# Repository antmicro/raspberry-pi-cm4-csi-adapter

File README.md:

# Antmicro's Raspberry Pi CM4 CSI adapter

Copyright (c) 2022 [Antmicro](https://www.antmicro.com)

## Overview

This repository contains open hardware design files for an adapter board allowing to connect video accessories developed by Antmicro to a Raspberry Pi CM4 IO Board over a 22-pin FFC connector.
The adapter allows to connect a 4-lane MIPI CSI-2 video interface along with power supply rail and I2C bus.  
The design files were prepared in KiCad.

## Repository structure

The main repository directory contains KiCad PCB project files, a LICENSE and README.
The remaining files are stored in the following directories:

* `lib` - contains the component libraries
* `img` - contains graphics for this README

## Key Features

* 50-pin FFC connector compatible with video accessories developed by Antmicro
* 22-pin FFC connector compatible with CSI video interface exposed on Raspberry Pi CM4 IO board
* Testpoints and jumper resistors for debugging the I2C communication

This adapter is electrically compatible with several video accessories created by Antmicro such as:
 
* [OV9281 Dual Camera Board](https://github.com/antmicro/ov9281-camera-board)
* [SDI-MIPI bridge](https://github.com/antmicro/sdi-mipi-bridge)
* [HDMI-MIPI bridge](https://github.com/antmicro/hdmi-mipi-bridge)

## License

[Apache-2.0](LICENSE)

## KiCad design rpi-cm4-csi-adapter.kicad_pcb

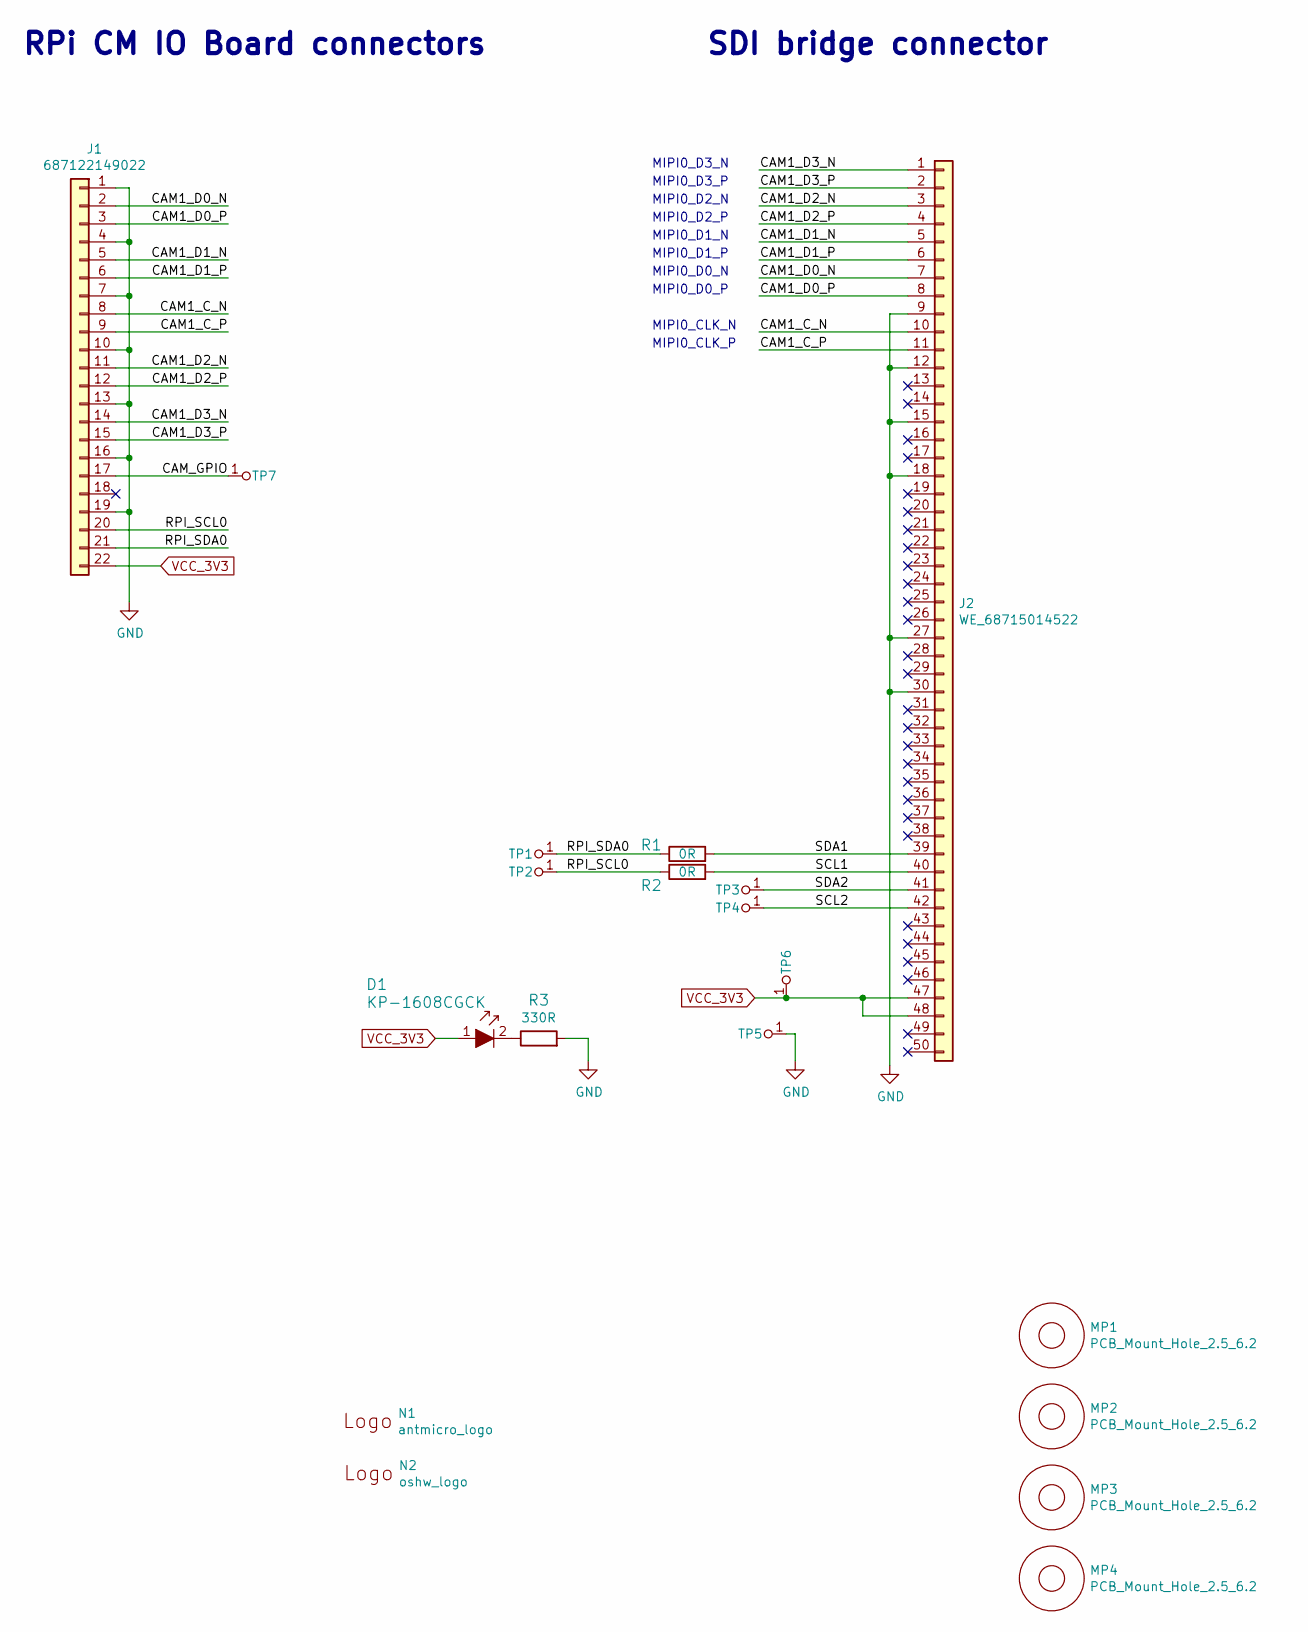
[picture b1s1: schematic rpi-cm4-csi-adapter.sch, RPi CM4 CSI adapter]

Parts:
D1: KP-1608CGCK; LED_0603; MPN KP-1608CGCK
J1: 687122149022; MPN 687122149022
J2: WE_68715014522; MPN 68715014522
MP1, MP2, MP3, MP4: PCB_Mount_Hole_2.5_6.2; Mount-hole-M2.5
N1: antmicro_logo; antmicro-logo_scaled_12mm
N2: oshw_logo; oshw-logo
R1, R2: R_0R_0402; 0402-res; MPN ERJ2GE0R00X
R3: R_330R_0402; 0402-res; MPN MCMR04X3300FTL
TP1, TP2, TP3, TP4, TP5, TP6, TP7: TP; TP-R-1.5

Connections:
/CAM1_C_N: J1.8, J2.10
/CAM1_C_P: J1.9, J2.11
/CAM1_D0_N: J1.2, J2.7
/CAM1_D0_P: J1.3, J2.8
/CAM1_D1_N: J1.5, J2.5
/CAM1_D1_P: J1.6, J2.6
/CAM1_D2_N: J1.11, J2.3
/CAM1_D2_P: J1.12, J2.4
/CAM1_D3_N: J1.14, J2.1
/CAM1_D3_P: J1.15, J2.2
/CAM_GPIO: J1.17, TP7.1
/RPI_SCL0: J1.20, R2.1, TP2.1
/RPI_SDA0: J1.21, R1.1, TP1.1
/SCL1: J2.40, R2.2
/SCL2: J2.42, TP4.1
/SDA1: J2.39, R1.2
/SDA2: J2.41, TP3.1
GND: J1.1, J1.4, J1.7, J1.10, J1.13, J1.16, J1.19, J2.9, J2.12, J2.15, J2.18, J2.27, J2.30, R3.2, TP5.1
unnamed: D1.2, R3.1
VCC_3V3: D1.1, J1.22, J2.47, J2.48, TP6.1

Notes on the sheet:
SDI bridge connector
RPi CM IO Board connectors
MIPI0_D1_N
MIPI0_D1_P
MIPI0_D0_N
MIPI0_D0_P
MIPI0_CLK_N
MIPI0_CLK_P
MIPI0_D2_P
MIPI0_D2_N
MIPI0_D3_P
MIPI0_D3_N

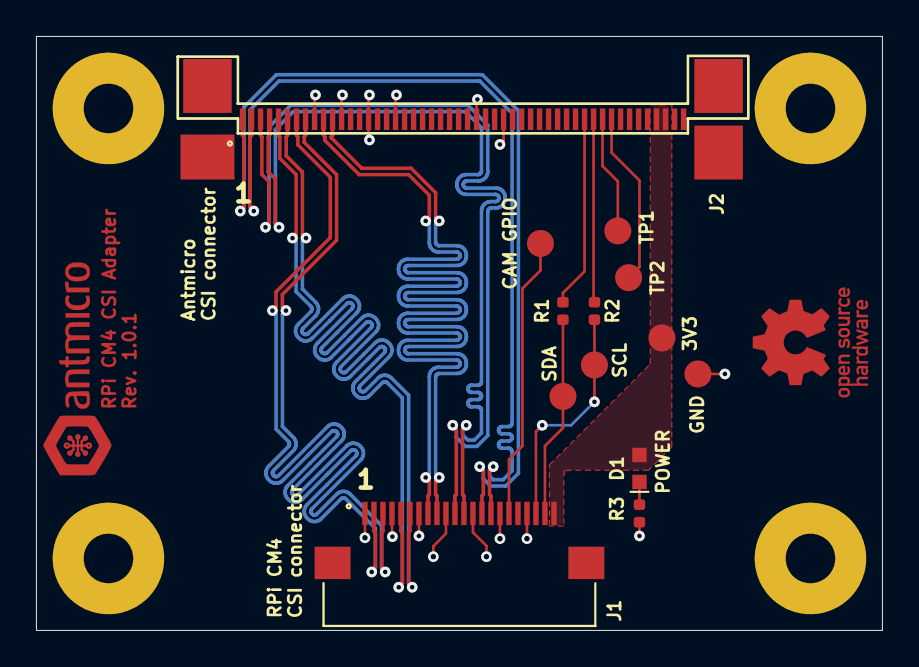
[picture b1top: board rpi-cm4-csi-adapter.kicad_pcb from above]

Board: 4 copper layers, 47.0 x 33.0 mm, 19 parts (0 on the bottom side), 20 nets.

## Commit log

2022-08-09 Initial commit.
2022-08-09 Make 687122149022 a SMT component
2022-08-09 Generate local libraries
2022-08-09 Swap I2C lines - bump revision to 1.0.1
2022-08-09 Add KiCad 6.0 project
2022-08-09 Add LICENSE
2022-08-09 Add README
2022-08-09 Add a photo with black background
2022-09-22 Notes added by 'git notes add'
